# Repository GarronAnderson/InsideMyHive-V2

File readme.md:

# STM32 Beehive Monitor

in active development

thanks to 
https://github.com/Reetabass/STM32-HAL-SX1276-LoRa 
for the LoRa libraries
and
https://github.com/libdriver/htu21d
for the htu21d driver

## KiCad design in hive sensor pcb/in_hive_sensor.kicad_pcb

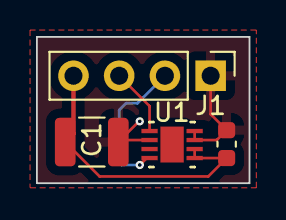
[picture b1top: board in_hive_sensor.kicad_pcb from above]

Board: 2 copper layers, 11.8 x 8.1 mm, 4 parts (0 on the bottom side), 4 nets.

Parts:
C1: 10uF; C_1210_3225Metric
C2: 100nF; C_0603_1608Metric
J1: in hive sensor; PinHeader_1x04_P2.54mm_Vertical
U1: HDC3022DEJR; DEJ0008A-C01-IPC_A

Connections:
+3V3: C1.1, C2.2, J1.4, U1.5 (VDD), U1.6 (RESET_N)
GND: C1.2, C2.1, J1.1, U1.2 (ADDR), U1.7 (ADDR1), U1.8 (GND)
SCL: J1.2, U1.4 (SCL)
SDA: J1.3, U1.1 (SDA)

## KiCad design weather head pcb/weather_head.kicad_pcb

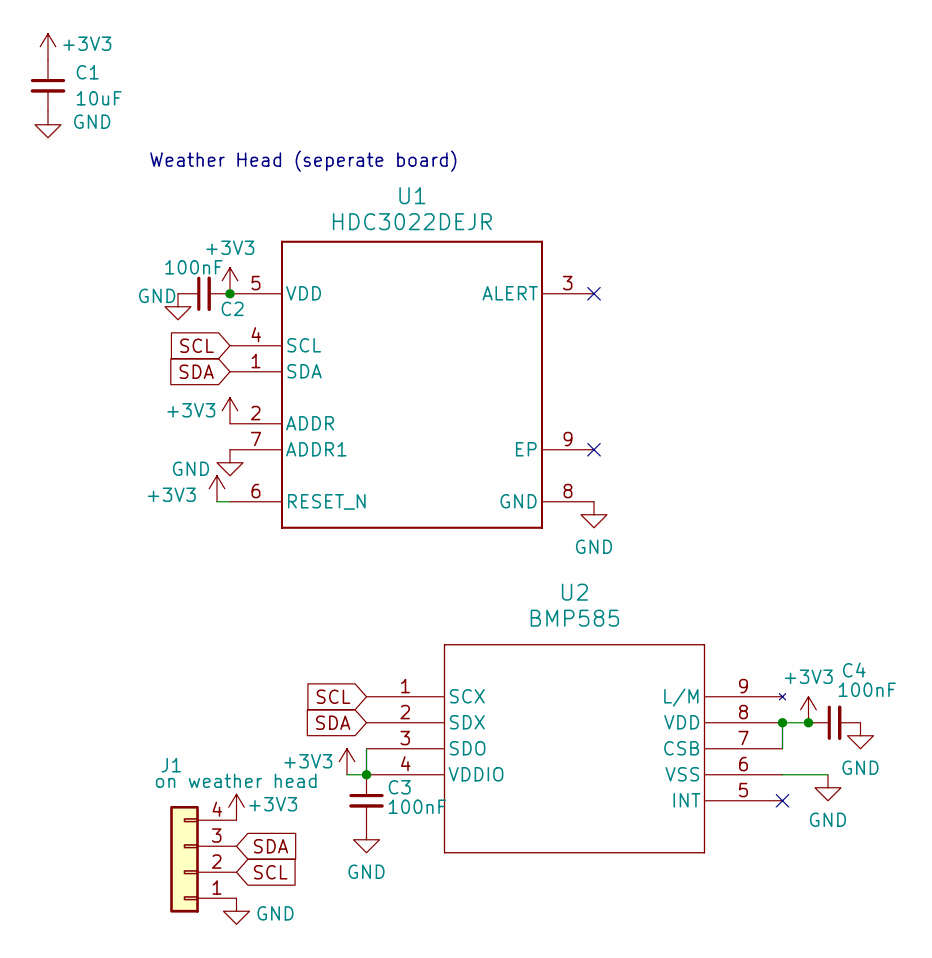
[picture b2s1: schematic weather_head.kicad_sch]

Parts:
C1: 10uF; C_1210_3225Metric
C2, C3, C4: 100nF; C_0603_1608Metric
J1: on weather head; PinHeader_1x04_P2.54mm_Vertical
U1: HDC3022DEJR; DEJ0008A-C01-IPC_A
U2: BMP585; LGA9_BMP585_BOS

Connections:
+3V3: C1.1, C2.2, C3.1, C4.1, J1.4, U1.2 (ADDR), U1.5 (VDD), U1.6 (RESET_N), U2.3 (SDO), U2.4 (VDDIO), U2.7 (CSB), U2.8 (VDD)
GND: C1.2, C2.1, C3.2, C4.2, J1.1, U1.7 (ADDR1), U1.8 (GND), U2.6 (VSS)
SCL: J1.2, U1.4 (SCL), U2.1 (SCX)
SDA: J1.3, U1.1 (SDA), U2.2 (SDX)

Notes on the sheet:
Weather Head (seperate board)

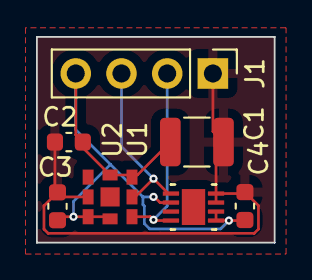
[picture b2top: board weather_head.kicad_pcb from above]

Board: 2 copper layers, 13.2 x 11.4 mm, 7 parts (0 on the bottom side), 4 nets.

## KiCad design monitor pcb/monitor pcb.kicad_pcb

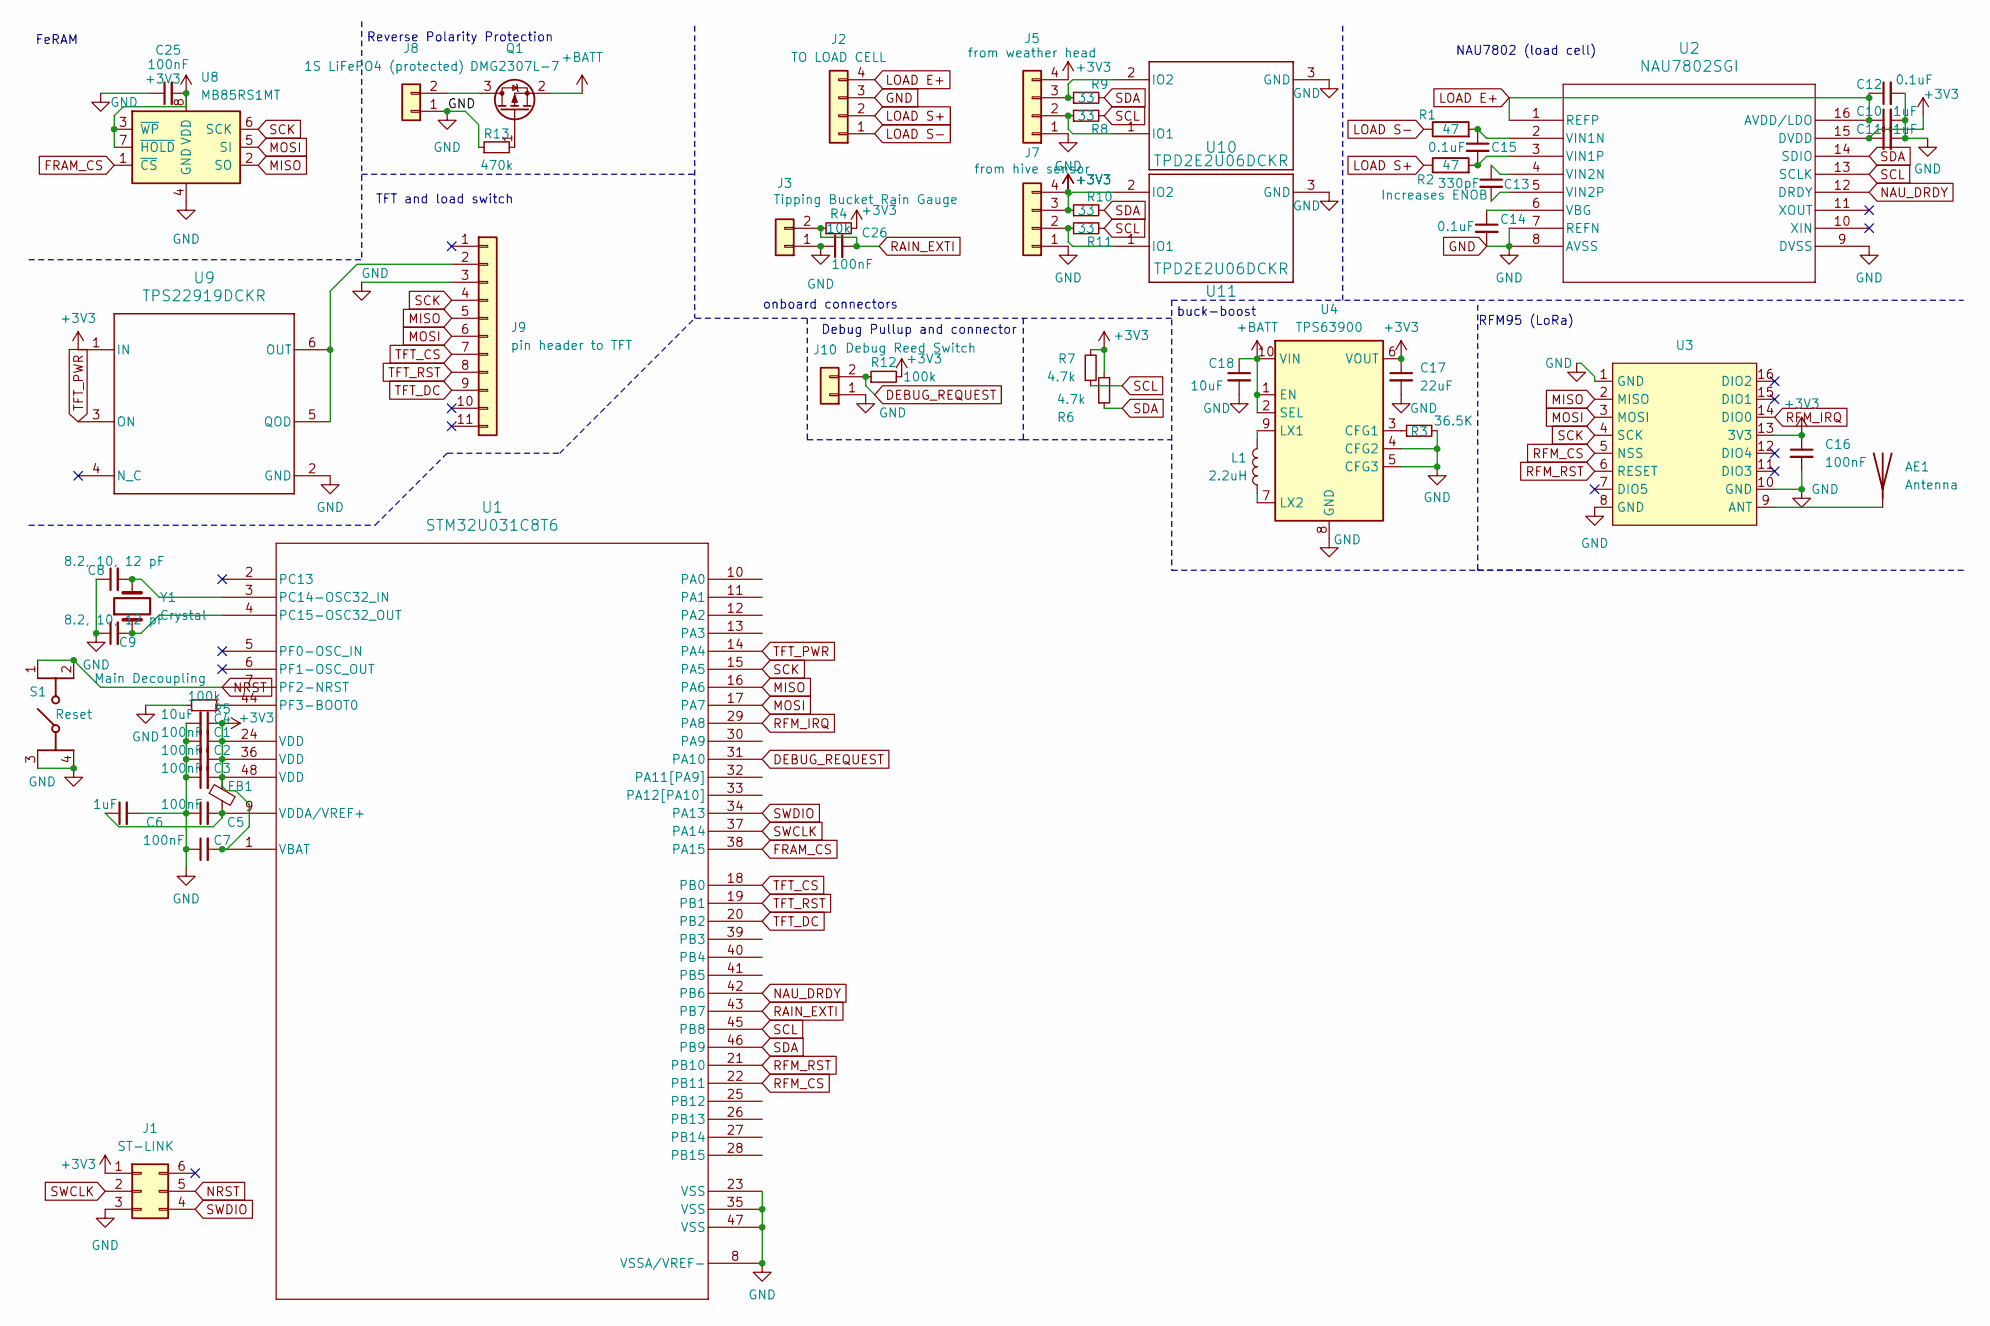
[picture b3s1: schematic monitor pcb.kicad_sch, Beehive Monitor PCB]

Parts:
AE1: Antenna; SMA_EDGELAUNCH
C1, C2, C3, C5, C7, C16, C25, C26: 100nF; C_0603_1608Metric
C4: 10uF; C_0805_2012Metric
C6: 1uF; C_0603_1608Metric
C8, C9: 8.2, 10, 12 pF; C_0402_1005Metric
C10, C11: 1uF; C_0805_2012Metric
C12, C14, C15: 0.1uF; C_0603_1608Metric
C13: 330pF; C_0402_1005Metric
C17: 22uF; C_1210_3225Metric
C18: 10uF; C_1210_3225Metric
FB1: FerriteBead_Small; L_0603_1608Metric
J1: Conn_02x03_Counter_Clockwise; PinHeader_2x03_P2.54mm_Vertical
J2: TO LOAD CELL; TerminalBlock_Phoenix_PT-1,5-4-3.5-H_1x04_P3.50mm_Horizontal
J3: Tipping Bucket Rain Gauge; TerminalBlock_Phoenix_PT-1,5-2-3.5-H_1x02_P3.50mm_Horizontal
J5: from weather head; TerminalBlock_Phoenix_PT-1,5-4-3.5-H_1x04_P3.50mm_Horizontal
J7: from hive sensor; TerminalBlock_Phoenix_PT-1,5-4-3.5-H_1x04_P3.50mm_Horizontal
J8: 1S LiFePO4 (protected); JST_PH_S2B-PH-K_1x02_P2.00mm_Horizontal
J9: pin header to TFT; PinHeader_1x11_P2.54mm_Vertical
J10: Debug Reed Switch; PinHeader_1x02_P2.54mm_Vertical
L1: 2.2uH; SRN3015TA2R2M
Q1: DMG2307L-7; SOT-23-3
R1, R2: 47; R_0603_1608Metric
R3: 36.5K; R_0603_1608Metric
R4: 10k; R_0603_1608Metric
R5, R12: 100k; R_0603_1608Metric
R6, R7: 4.7k; R_0603_1608Metric
R8, R9, R10, R11: 33; R_0603_1608Metric
R13: 470k; R_0603_1608Metric
S1: PTS647SN38SMTR2_LFS; PTS647SM38SMTR2LFS; Manufacturer_Part_Number PTS647SN38SMTR2 LFS
U1: STM32U031C8T6; LQFP-48_7x7mm_P0.5mm
U2: NAU7802SGI; SOIC-16_3.9x9.9mm_P1.27mm
U3: RFM95W
U4: TPS63900; WSON-10-1EP_2.5x2.5mm_P0.5mm_EP1.2x2mm_ThermalVias
U8: MB85RS1MT; SOIC-8_3.9x4.9mm_P1.27mm
U9: TPS22919DCKR; SOT-363_SC-70-6
U10, U11: TPD2E2U06DCKR; SOT-323_SC-70
Y1: Crystal; Crystal_SMD_2012-2Pin_2.0x1.2mm

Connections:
+3V3: C1.2, C2.2, C3.2, C4.1, C7.2, C11.1, C16.1, C17.1, C25.2, FB1.1, J1.1, J5.4, J7.4, R4.2, R6.2, R7.2, R12.2, U1.1 (VBAT), U1.24 (VDD), U1.36 (VDD), U1.48 (VDD), U2.15 (DVDD), U3.13 (3V3), U4.6 (VOUT), U8.3 (~WP), U8.7 (~HOLD), U8.8 (VDD), U9.1 (IN)
+BATT: C18.1, Q1.2 (S), U4.1 (EN), U4.2 (SEL), U4.10 (VIN)
DEBUG_REQUEST: J10.2, R12.1, U1.31 (PA10)
FRAM_CS: U1.38 (PA15), U8.1 (~CS)
GND: AE1.GND@1, AE1.GND@2, AE1.GND@3, AE1.GND@4, C1.1, C2.1, C3.1, C4.2, C5.1, C6.2, C7.1, C8.1, C9.1, C10.2, C11.2, C12.2, C14.2, C16.2, C17.2, C18.2, C25.1, C26.1, J1.3, J2.3, J3.1, J5.1, J7.1, J8.1, J9.3, J10.1, R3.2, R5.1, R13.1, S1.3 (COM_1), S1.4 (COM_2), U1.8 (VSSA/VREF-), U1.23 (VSS), U1.35 (VSS), U1.47 (VSS), U2.7 (REFN), U2.8 (AVSS), U2.9 (DVSS), U3.1 (GND), U3.8 (GND), U3.10 (GND), U4.4 (CFG2), U4.5 (CFG3), U4.8 (GND), U4.11 (GND), U8.4 (GND), U9.2 (GND), U10.3 (GND), U11.3 (GND)
LOAD E+: C10.1, C12.1, J2.4, U2.1 (REFP), U2.16 (AVDD/LDO)
LOAD S+: J2.2, R2.1
LOAD S-: J2.1, R1.1
MISO: J9.5, U1.16 (PA6), U3.2 (MISO), U8.2 (SO)
MOSI: J9.6, U1.17 (PA7), U3.3 (MOSI), U8.5 (SI)
NAU_DRDY: U1.42 (PB6), U2.12 (DRDY)
NRST: J1.5, S1.1 (NO_1), S1.2 (NO_2), U1.7 (PF2-NRST)
unnamed: AE1.1, AE1.P, U3.9 (ANT)
unnamed: J5.2, R8.1, U10.1 (IO1)
unnamed: J5.3, R9.1, U10.2 (IO2)
unnamed: J7.2, R11.1, U11.1 (IO1)
unnamed: J7.3, R10.1, U11.2 (IO2)
unnamed: J8.2, Q1.3 (D)
unnamed: J9.2, U9.5 (QOD), U9.6 (OUT)
unnamed: Q1.1 (G), R13.2
unnamed: C8.2, U1.3 (PC14-OSC32_IN), Y1.2
unnamed: C9.2, U1.4 (PC15-OSC32_OUT), Y1.1
unnamed: R5.2, U1.44 (PF3-BOOT0)
unnamed: C5.2, C6.1, FB1.2, U1.9 (VDDA/VREF+)
unnamed: C14.1, U2.6 (VBG)
unnamed: C15.1, R1.2, U2.2 (VIN1N)
unnamed: C15.2, R2.2, U2.3 (VIN1P)
unnamed: C13.1, U2.4 (VIN2N)
unnamed: C13.2, U2.5 (VIN2P)
unnamed: R3.1, U4.3 (CFG1)
unnamed: L1.2, U4.9 (LX1)
unnamed: L1.1, U4.7 (LX2)
RAIN_EXTI: C26.2, J3.2, R4.1, U1.43 (PB7)
RFM_CS: U1.22 (PB11), U3.5 (NSS)
RFM_IRQ: U1.29 (PA8), U3.14 (DIO0)
RFM_RST: U1.21 (PB10), U3.6 (RESET)
SCK: J9.4, U1.15 (PA5), U3.4 (SCK), U8.6 (SCK)
SCL: R7.1, R8.2, R11.2, U1.45 (PB8), U2.13 (SCLK)
SDA: R6.1, R9.2, R10.2, U1.46 (PB9), U2.14 (SDIO)
SWCLK: J1.2, U1.37 (PA14)
SWDIO: J1.4, U1.34 (PA13)
TFT_CS: J9.7, U1.18 (PB0)
TFT_DC: J9.9, U1.20 (PB2)
TFT_PWR: U1.14 (PA4), U9.3 (ON)
TFT_RST: J9.8, U1.19 (PB1)

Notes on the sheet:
Debug Pullup and connector
onboard connectors
FeRAM
RFM95 (LoRa)
Reverse Polarity Protection
buck-boost
NAU7802 (load cell)
TFT and load switch

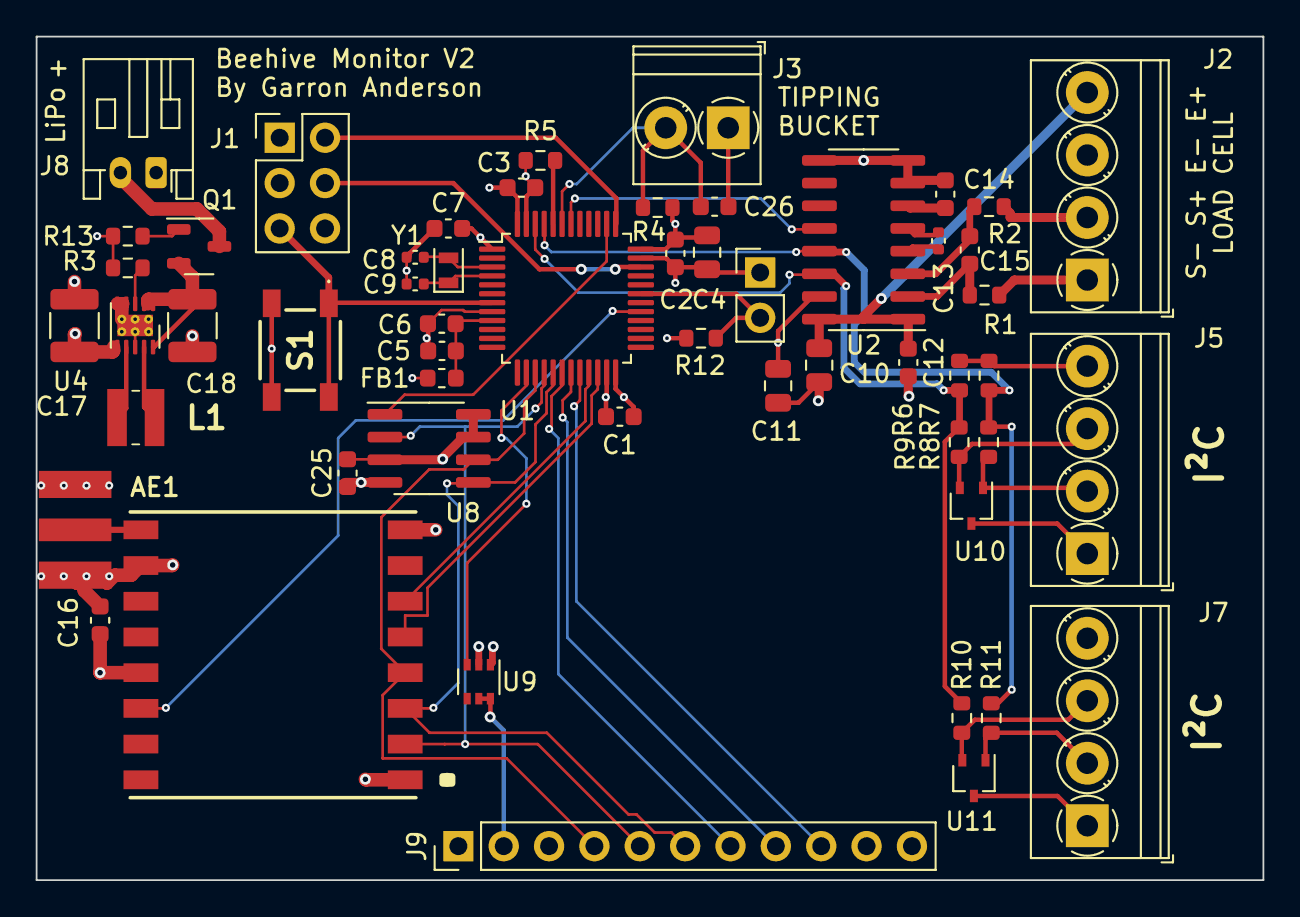
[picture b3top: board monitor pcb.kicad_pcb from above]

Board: 4 copper layers, 68.7 x 47.2 mm, 55 parts (0 on the bottom side), 45 nets.

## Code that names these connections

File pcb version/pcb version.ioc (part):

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Mcu.Name=STM32U031C8Tx
Mcu.Package=LQFP48
Mcu.UserName=STM32U031C8Tx
PA10.GPIOParameters=GPIO_Label,GPIO_ModeDefaultEXTI
PA10.GPIO_Label=DEBUG_REQUEST
PA10.GPIO_ModeDefaultEXTI=GPIO_MODE_IT_RISING_FALLING
PA10.Signal=GPXTI10
PA13\ (SWDIO).Mode=Serial_Wire
PA13\ (SWDIO).Signal=DEBUG_JTMS-SWDIO
PA14\ (SWCLK).Mode=Serial_Wire
PA14\ (SWCLK).Signal=DEBUG_JTCK-SWCLK
PA15.GPIOParameters=GPIO_Label
PA15.GPIO_Label=FRAM_CS
PA15.Signal=GPIO_Output
PA4.GPIOParameters=GPIO_Label
PA4.GPIO_Label=TFT_PWR
PA4.Signal=GPIO_Output
PA5.Mode=Full_Duplex_Master
PA5.Signal=SPI1_SCK
PA6.Mode=Full_Duplex_Master
PA6.Signal=SPI1_MISO
PA7.Mode=Full_Duplex_Master
PA7.Signal=SPI1_MOSI
PA8.GPIOParameters=GPIO_Label,GPIO_ModeDefaultEXTI
PA8.GPIO_Label=RFM_IRQ
PA8.GPIO_ModeDefaultEXTI=GPIO_MODE_IT_RISING_FALLING
PA8.Signal=GPXTI8
PB0.GPIOParameters=GPIO_Label
PB0.GPIO_Label=TFT_CS
PB0.Signal=GPIO_Output
PB1.GPIOParameters=GPIO_Label
PB1.GPIO_Label=TFT_RST
PB1.Signal=GPIO_Output
PB10.GPIOParameters=GPIO_Label
PB10.GPIO_Label=RFM_RST
PB10.Signal=GPIO_Output
PB11.GPIOParameters=GPIO_Label
PB11.GPIO_Label=RFM_CS
PB11.Signal=GPIO_Output
PB2.GPIOParameters=GPIO_Label
PB2.GPIO_Label=TFT_DC
PB2.Signal=GPIO_Output
PB6.GPIOParameters=GPIO_Label,GPIO_ModeDefaultEXTI
PB6.GPIO_Label=NAU_DRDY
PB6.GPIO_ModeDefaultEXTI=GPIO_MODE_IT_RISING_FALLING
PB6.Signal=GPXTI6
PB7.GPIOParameters=GPIO_Label,GPIO_ModeDefaultEXTI
PB7.GPIO_Label=RAIN_EXTI
PB7.GPIO_ModeDefaultEXTI=GPIO_MODE_IT_RISING_FALLING
PB7.Signal=GPXTI7
PB8.Mode=I2C
PB8.Signal=I2C1_SCL
PB9.Mode=I2C
PB9.Signal=I2C1_SDA
PC14-OSC32_IN.Mode=LSE-External-Oscillator
PC14-OSC32_IN.Signal=RCC_OSC32_IN
PC15-OSC32_OUT.Mode=LSE-External-Oscillator
PC15-OSC32_OUT.Signal=RCC_OSC32_OUT
RCC.HSE_VALUE=4000000
RCC.SYSCLKFreq_VALUE=16000000
board=custom
